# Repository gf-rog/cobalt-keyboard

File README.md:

# Cobalt keyboard
- 6x4+3 split keyboard
- reversible
- low-profile
- supports 128x32 OLED screens
- uses the STM32F103C8 Blue Pill board

## Credits
Kailh Choc footprint (modified):
https://github.com/daprice/keyswitches.pretty
Creative Commons Attribution-ShareAlike 4.0 International License

Blue Pill footprint (modified):
https://github.com/erichelgeson/Kicad-STM32
No license given

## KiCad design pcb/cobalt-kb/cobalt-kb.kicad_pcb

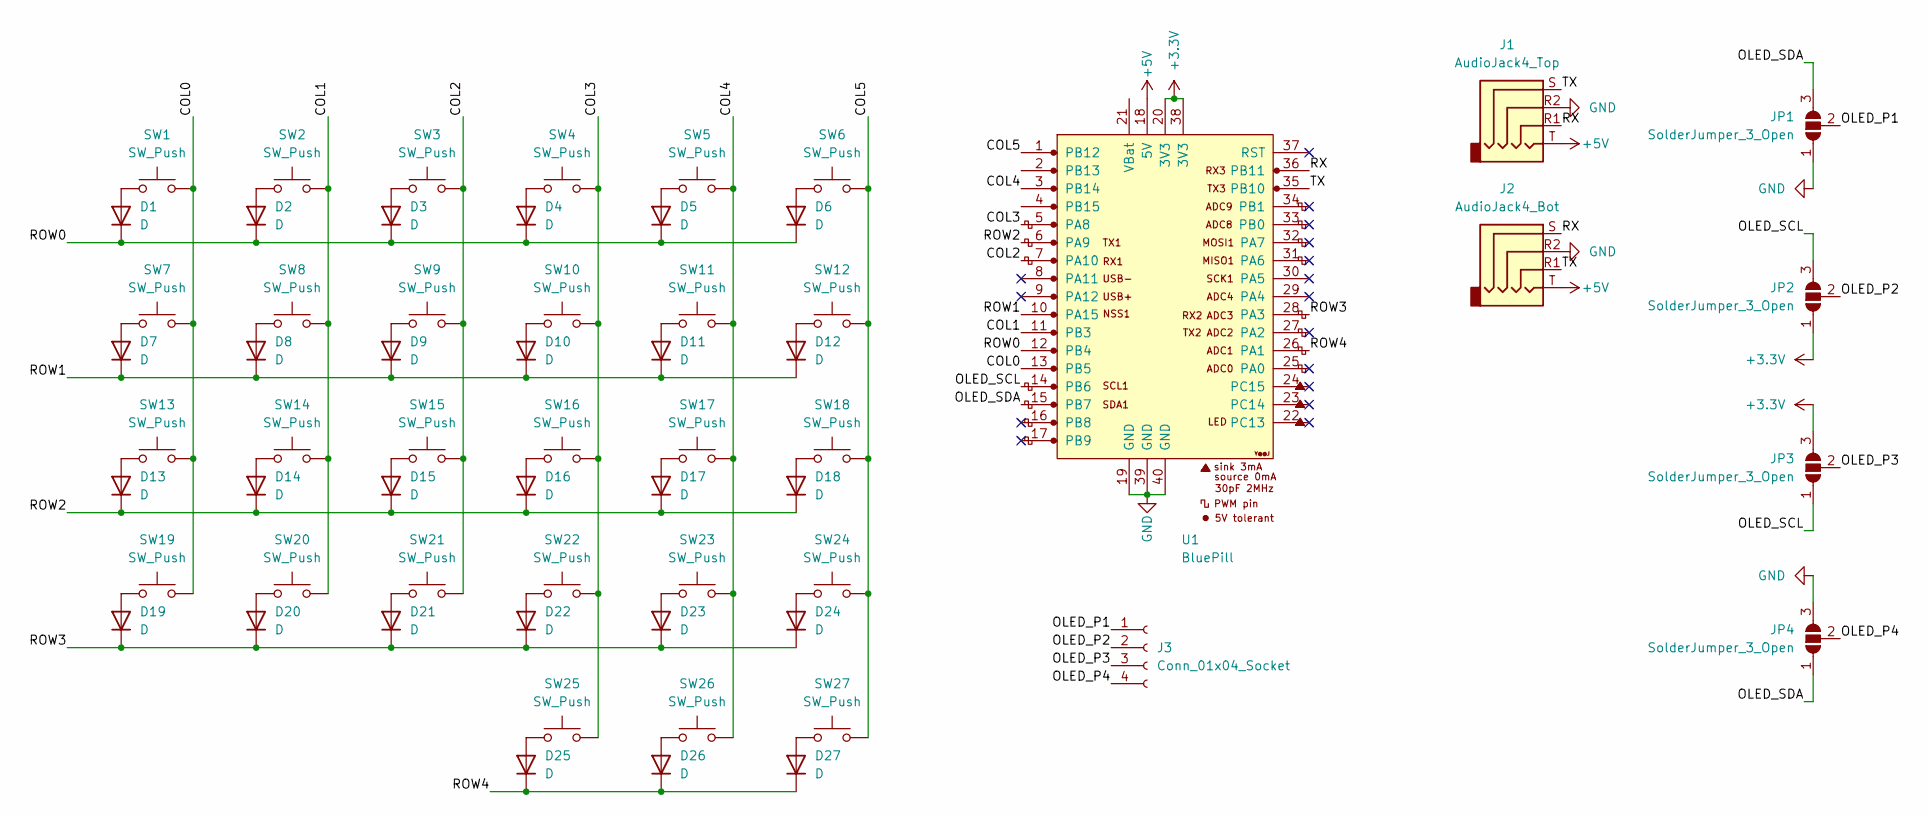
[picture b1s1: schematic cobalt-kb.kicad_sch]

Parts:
D1, D2, D3, D4, D5, D6, D7, D8, D9, D10, D11, D12, D13, D14, D15, D16, D17, D18, D19, D20, D21, D22, D23, D24, D25, D26, D27: D; D_SOD-123_Reversible
J1: AudioJack4_Top; Jack_3.5mm_PJ320D_Horizontal
J2: AudioJack4_Bot; Jack_3.5mm_PJ320D_Horizontal
J3: Conn_01x04_Socket; PinSocket_1x04_P2.54mm_Vertical
JP1, JP2, JP3, JP4: SolderJumper_3_Open; SolderJumper-3_P1.3mm_Open_RoundedPad1.0x1.5mm_FrontBack
SW1, SW2, SW3, SW4, SW5, SW6, SW7, SW8, SW9, SW10, SW11, SW12, SW13, SW14, SW15, SW16, SW17, SW18, SW19, SW20, SW21, SW22, SW23, SW24, SW25, SW26, SW27: SW_Push; Kailh_Socket_PG1350_Reversible
U1: BluePill; BluePill_Socket_Simplified

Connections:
+3.3V: JP2.1 (A), JP3.3 (B), U1.20 (3V3), U1.38 (3V3)
+5V: J1.T, J2.T, U1.18 (5V)
/COL0: SW1.2, SW7.2, SW13.2, SW19.2, U1.13 (PB5)
/COL1: SW2.2, SW8.2, SW14.2, SW20.2, U1.11 (PB3)
/COL2: SW3.2, SW9.2, SW15.2, SW21.2, U1.7 (PA10)
/COL3: SW4.2, SW10.2, SW16.2, SW22.2, SW25.2, U1.5 (PA8)
/COL4: SW5.2, SW11.2, SW17.2, SW23.2, SW26.2, U1.3 (PB14)
/COL5: SW6.2, SW12.2, SW18.2, SW24.2, SW27.2, U1.1 (PB12)
/OLED_P1: J3.1, JP1.2 (C)
/OLED_P2: J3.2, JP2.2 (C)
/OLED_P3: J3.3, JP3.2 (C)
/OLED_P4: J3.4, JP4.2 (C)
/OLED_SCL: JP2.3 (B), JP3.1 (A), U1.14 (PB6)
/OLED_SDA: JP1.3 (B), JP4.1 (A), U1.15 (PB7)
/ROW0: D1.1 (K), D2.1 (K), D3.1 (K), D4.1 (K), D5.1 (K), D6.1 (K), U1.12 (PB4)
/ROW1: D7.1 (K), D8.1 (K), D9.1 (K), D10.1 (K), D11.1 (K), D12.1 (K), U1.10 (PA15)
/ROW2: D13.1 (K), D14.1 (K), D15.1 (K), D16.1 (K), D17.1 (K), D18.1 (K), U1.6 (PA9)
/ROW3: D19.1 (K), D20.1 (K), D21.1 (K), D22.1 (K), D23.1 (K), D24.1 (K), U1.28 (PA3)
/ROW4: D25.1 (K), D26.1 (K), D27.1 (K), U1.26 (PA1)
/RX: J1.R1, J2.S, U1.36 (PB11)
/TX: J1.S, J2.R1, U1.35 (PB10)
GND: J1.R2, J2.R2, JP1.1 (A), JP4.3 (B), U1.19 (GND), U1.39 (GND), U1.40 (GND)
unnamed: D1.2 (A), SW1.1
unnamed: D2.2 (A), SW2.1
unnamed: D3.2 (A), SW3.1
unnamed: D4.2 (A), SW4.1
unnamed: D5.2 (A), SW5.1
unnamed: D6.2 (A), SW6.1
unnamed: D7.2 (A), SW7.1
unnamed: D8.2 (A), SW8.1
unnamed: D9.2 (A), SW9.1
unnamed: D10.2 (A), SW10.1
unnamed: D11.2 (A), SW11.1
unnamed: D12.2 (A), SW12.1
unnamed: D13.2 (A), SW13.1
unnamed: D14.2 (A), SW14.1
unnamed: D15.2 (A), SW15.1
unnamed: D16.2 (A), SW16.1
unnamed: D17.2 (A), SW17.1
unnamed: D18.2 (A), SW18.1
unnamed: D19.2 (A), SW19.1
unnamed: D20.2 (A), SW20.1
unnamed: D21.2 (A), SW21.1
unnamed: D22.2 (A), SW22.1
unnamed: D23.2 (A), SW23.1
unnamed: D24.2 (A), SW24.1
unnamed: D25.2 (A), SW25.1
unnamed: D26.2 (A), SW26.1
unnamed: D27.2 (A), SW27.1

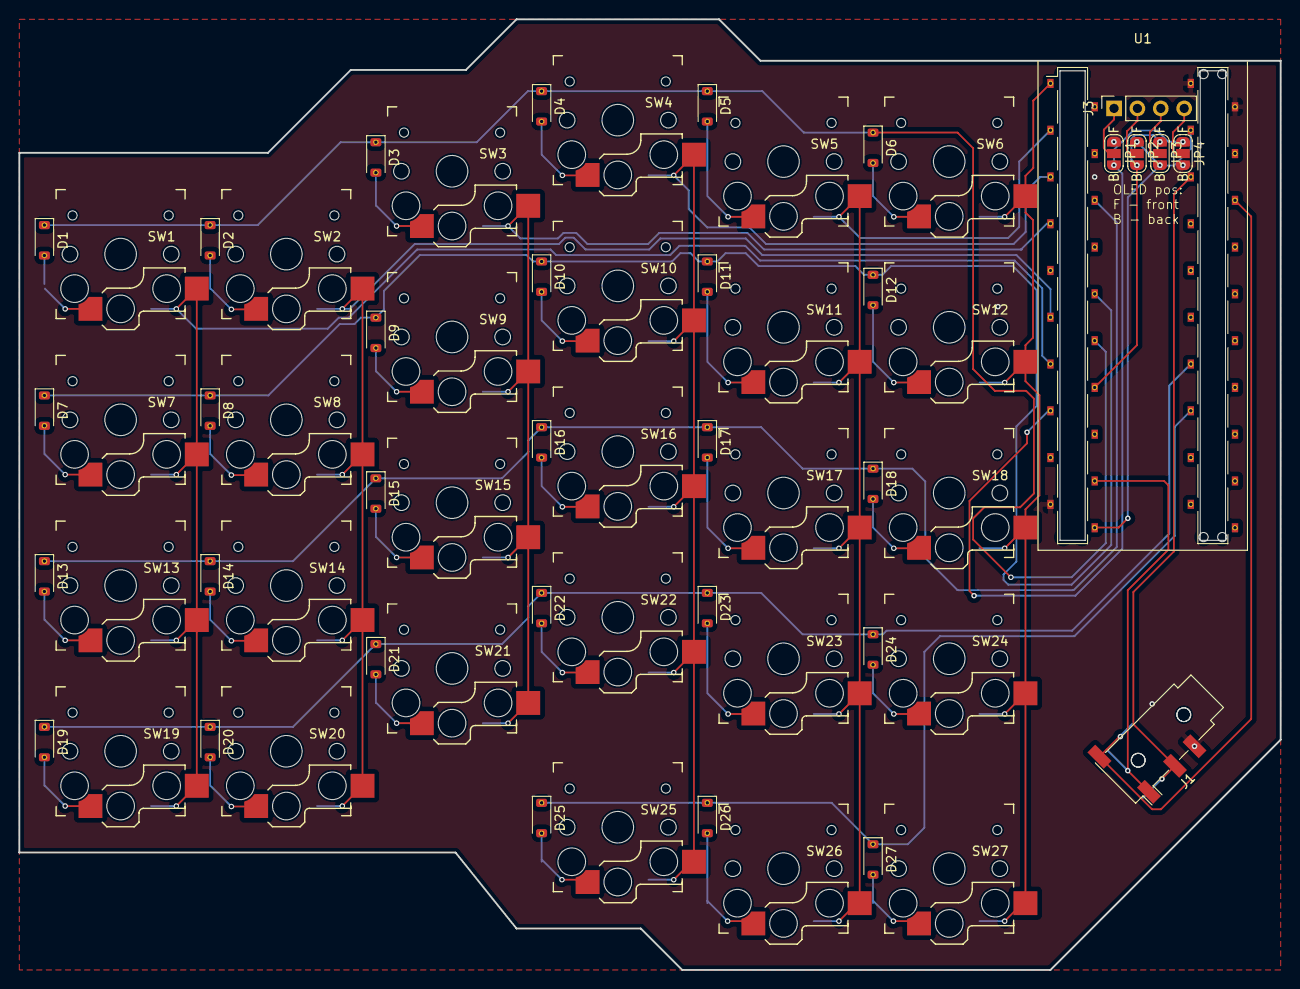
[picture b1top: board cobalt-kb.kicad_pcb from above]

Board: 2 copper layers, 137.0 x 103.2 mm, 62 parts (1 on the bottom side), 49 nets.
